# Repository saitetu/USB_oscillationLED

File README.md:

# USB_oscillationLED
USB直挿し型のLED発振回路です。
２石型です。
Eagle CADです。

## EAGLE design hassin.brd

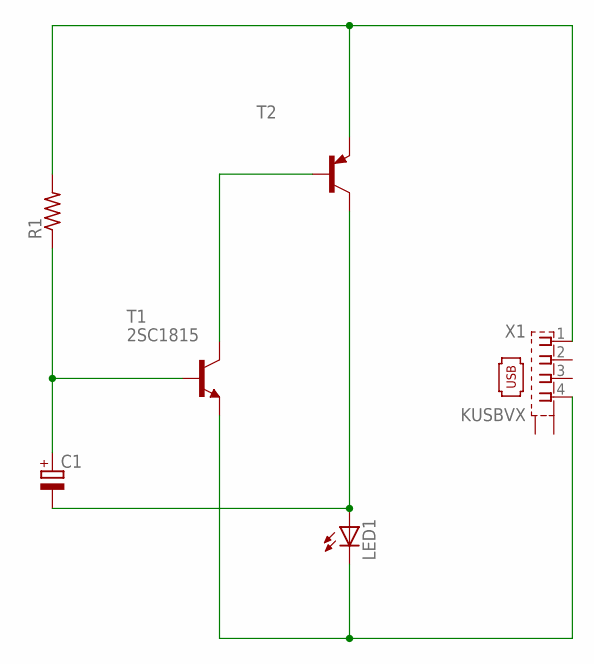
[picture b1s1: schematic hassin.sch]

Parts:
C1: CPOL-EUE2-5; E2-5
LED1: LED5MM
R1: R-US_0207/7; 0207/7
T1: 2SC1815; TO92-ECB
T2: 2SC1815-PNP-TO92-BCE; TO92-BCE
X1: KUSBVX

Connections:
unnamed: T1.C, T2.B
unnamed: LED1.K (C), T1.E, X1.4
unnamed: C1.-, LED1.A, T2.C
unnamed: R1.2, T2.E, X1.1
unnamed: C1.+, R1.1, T1.B

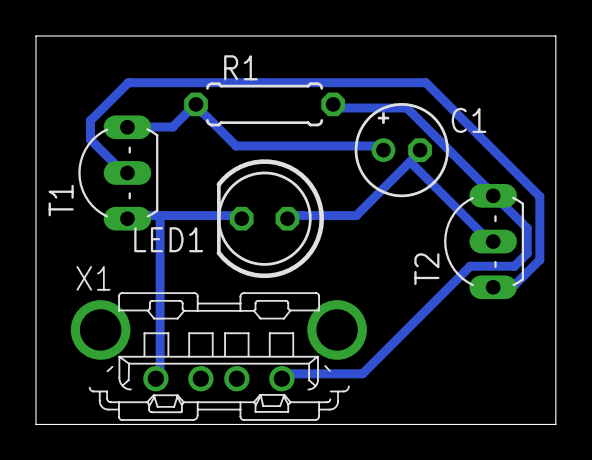
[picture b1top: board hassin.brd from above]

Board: 2 copper layers, 28.9 x 21.6 mm, 6 parts (0 on the bottom side), 5 nets.
